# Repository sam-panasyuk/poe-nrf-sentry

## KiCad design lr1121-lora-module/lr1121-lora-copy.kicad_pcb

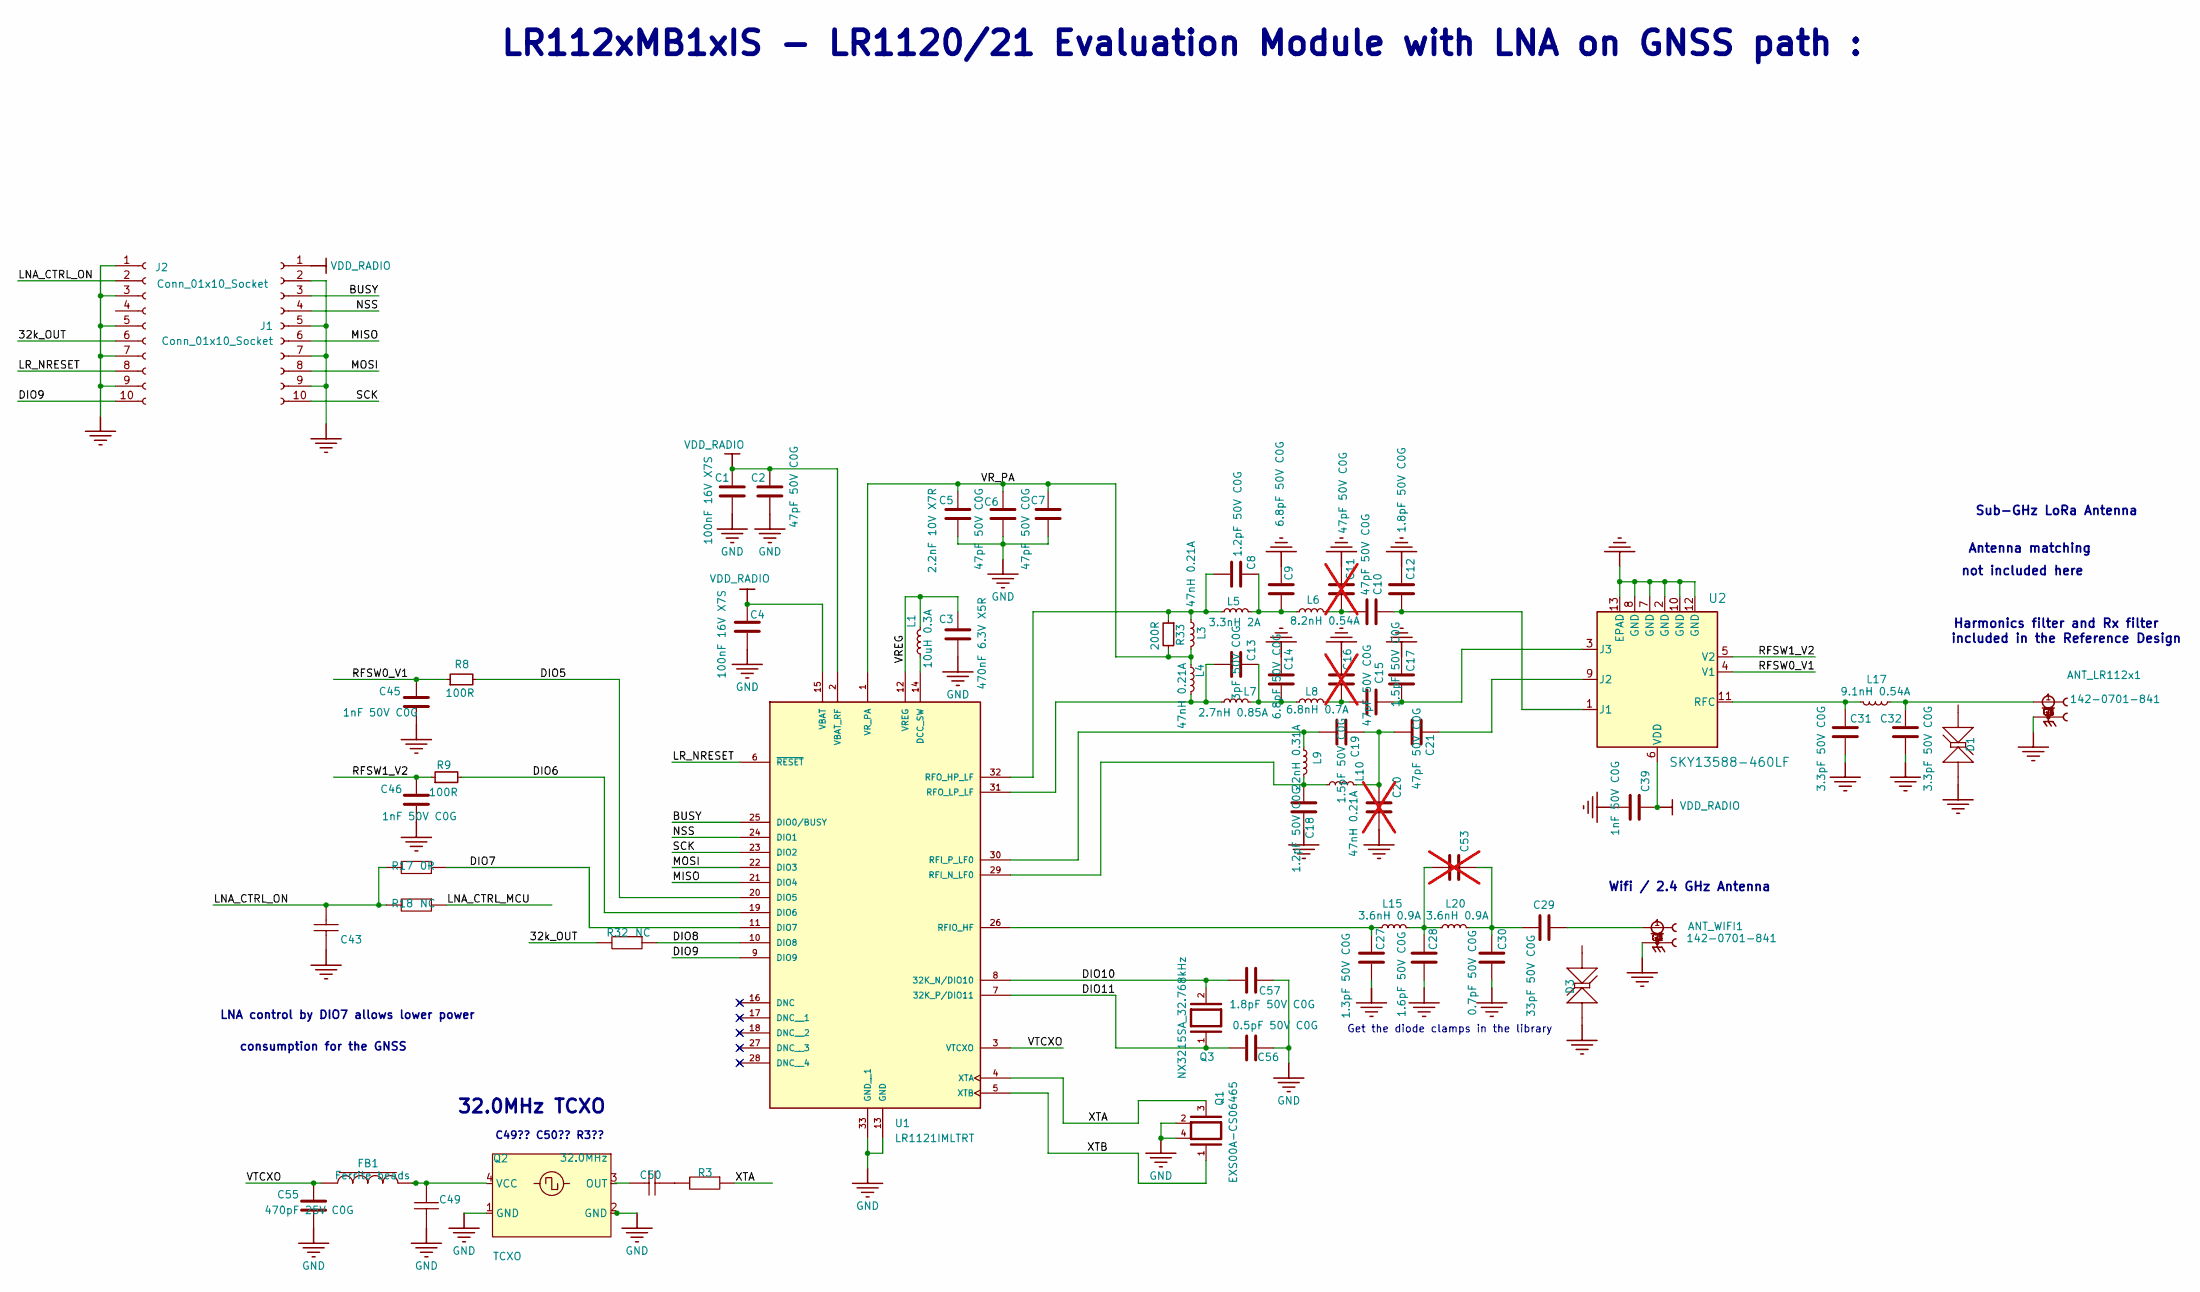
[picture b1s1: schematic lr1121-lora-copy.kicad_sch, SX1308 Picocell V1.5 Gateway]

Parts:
ANT_LR112x1: 142-0701-841; JOHNSON_142-0701-841; MPN 142-0701-841
ANT_WIFI1: 142-0701-841; JOHNSON_142-0701-841; MPN 142-0701-841
C1, C4: 100nF 16V X7S; C_0201_0603Metric; MPN GRM033C71C104ME14D; JLCPN C907967
C2, C6, C7, C10: 47pF 50V C0G; C_0201_0603Metric; MPN GRM0335C1H470GA01D; JLCPN C384994
C3: 470nF 6.3V X5R; C_0201_0603Metric; MPN GRM033R60J474KE90D; JLCPN C85926
C5: 2.2nF 10V X7R; C_0201_0603Metric; MPN GRM033R71A222KA01D; JLCPN C161479
C8, C18: 1.2pF 50V C0G; C_0402_1005Metric; MPN GRM1555C1H1R2BA01D
C9, C14: 6.8pF 50V C0G; C_0402_1005Metric; MPN GRM1555C1H6R8CA01D
C11: 47pF 50V C0G; C_0201_0603Metric; MPN GRM0335C1H470GA01D; JLCPN C384994; not fitted
C12: 1.8pF 50V C0G; C_0402_1005Metric; MPN GRM1555C1H1R8BA01D
C13: 3pF 50V C0G; C_0402_1005Metric; MPN GRM1555C1H3R0BA01J
C15, C21: 47pF 50V C0G; C_0402_1005Metric; MPN GRM1555C1H470JA01D
C16: 47pF 50V C0G; C_0402_1005Metric; MPN GRM1555C1H470JA01D; not fitted
C17, C19: 1.5pF 50V C0G; C_0402_1005Metric; MPN GRM1555C1H1R5BA01D; JLCPN C76957
C20: 1.5pF 50V C0G; C_0402_1005Metric; MPN GRM1555C1H1R5BA01D; JLCPN C76957; not fitted
C27: 1.3pF 50V C0G; C_0402_1005Metric; MPN GRM1555C1H1R3BA01D
C28: 1.6pF 50V C0G; C_0402_1005Metric; MPN GRM1555C1H1R6BA01D; JLCPN C88923
C29: 33pF 50V C0G; C_0402_1005Metric; MPN CL05C330JB5NNNC; JLCPN C70465
C30: 0.7pF 50V C0G; C_0402_1005Metric; MPN GRM1555C1HR70BA01D
C31, C32: 3.3pF 50V C0G; C_0402_1005Metric
C39, C45, C46: 1nF 50V C0G; C_0402_1005Metric; MPN C1005C0G1H102JT000F; JLCPN C343060
C43: c_201_smd
C49, C50: Cap; c_201_smd
C53: 820nF 25V X5R; C_0402_1005Metric; not fitted
C55: 470pF 25V C0G; C_0201_0603Metric; MPN GRM0335C1E471JA01D; JLCPN C161390
C56: 0.5pF 50V C0G; C_0201_0603Metric; MPN GRM0335C1HR50BA01D; JLCPN C85920
C57: 1.8pF 50V C0G; C_0201_0603Metric; MPN GRM0335C1H1R8BA01D; JLCPN C161415
D1, D3: TVS Diode; SLP0603P2X3F
FB1: Ferrite beads; Ferrite_201_smd
J1, J2: Conn_01x10_Socket; PinHeader_1x10_P2.00mm_Vertical
L1: 10uH 0.3A; L_0603_1608Metric; MPN MLZ1608N100LT000; JLCPN C194437
L3, L4, L10: 47nH 0.21A; L_0402_1005Metric; MPN LQW15AN47NJ00D; JLCPN C192855
L5: 3.3nH 2A; L_0402_1005Metric; MPN LQW15AN3N3C80D; JLCPN C237574
L6: 8.2nH 0.54A; L_0402_1005Metric; MPN LQW15AN8N2J00D; JLCPN C98066
L7: 2.7nH 0.85A; L_0402_1005Metric; MPN LQW15AN2N7C00D; JLCPN C98058
L8: 6.8nH 0.7A; L_0402_1005Metric; MPN LQW15AN6N8J00D; JLCPN C113119
L9: 22nH 0.31A; L_0402_1005Metric; MPN LQW15AN22NH00D; JLCPN C703122
L15, L20: 3.6nH 0.9A; L_0402_1005Metric; MPN LQW15AN3N6C10D; JLCPN C408158
L17: 9.1nH 0.54A; L_0402_1005Metric; MPN LQW15AN9N1J00D; JLCPN C437364
Q1: EXS00A-CS06465; Crystal_SMD_2016-4Pin_2.0x1.6mm; MPN EXS00A-CS06465; JLCPN C1986260
Q2: TCXO; TCXO 2.0x1.6mm
Q3: NX3215SA_32.768kHz; Crystal_SMD_3215-2Pin_3.2x1.5mm; MPN NX3215SA 32.768kHz; JLCPN C519280
R3, R32: Resistor; r_201_smd
R8, R9: 100R; R_0201_0603Metric; MPN RC0201FR-07100RL; JLCPN C77623
R17, R18: r_201_smd
R33: 200R; R_0201_0603Metric; MPN RC0201FR-07200RL
U1: LR1121IMLTRT; QFN-32-1EP_5x5mm_P0.5mm_EP3.7x3.7mm_ThermalVias; MPN LR1121IMLTRT; JLCPN C7498014
U2: SKY13588-460LF; QFN12_SKY; MPN SKY13588-460LF; JLCPN C2151906

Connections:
/32k_OUT: J2.6, R32.2
/BUSY: J1.3, U1.25 (DIO0/BUSY)
/DIO5: R8.2, U1.20 (DIO5)
/DIO6: R9.2, U1.19 (DIO6)
/DIO7: R17.2, U1.11 (DIO7)
/DIO8: R32.1, U1.10 (DIO8)
/DIO9: J2.10, U1.9 (DIO9)
/DIO10: C57.1, Q3.2, U1.8 (32K_N/DIO10)
/DIO11: C56.2, Q3.1, U1.7 (32K_P/DIO11)
/LNA_CTRL_MCU: R18.2
/LNA_CTRL_ON: C43.2, J2.2, R17.1, R18.1
/LR_NRESET: J2.8, U1.6 (~RESET)
/MISO: J1.6, U1.21 (DIO4)
/MOSI: J1.8, U1.22 (DIO3)
/NSS: J1.4, U1.24 (DIO1)
/RFSW0_V1: C45.2, R8.1, U2.4 (V1)
/RFSW1_V2: C46.2, R9.1, U2.5 (V2)
/SCK: J1.10, U1.23 (DIO2)
/VREG: C3.2, L1.1, U1.12 (VREG)
/VR_PA: C5.2, C6.2, C7.2, L3.2, L4.1, R33.2, U1.1 (VR_PA)
/VTCXO: C55.2, FB1.1, U1.3 (VTCXO)
/XTA: Q1.3, R3.1, U1.4 (XTA)
/XTB: Q1.1, U1.5 (XTB)
GND: ANT_LR112x1.G1, ANT_LR112x1.G2, ANT_LR112x1.G3, ANT_LR112x1.G4, ANT_WIFI1.G1, ANT_WIFI1.G2, ANT_WIFI1.G3, ANT_WIFI1.G4, C1.1, C2.1, C3.1, C4.1, C5.1, C6.1, C7.1, C9.2, C11.2, C12.2, C14.2, C16.2, C17.2, C18.1, C20.1, C27.1, C28.1, C30.1, C31.2, C32.2, C39.1, C43.1, C45.1, C46.1, C49.1, C55.1, C56.1, C57.2, D1.1 (A_1), D3.1 (A_1), J1.2, J1.5, J1.7, J1.9, J2.1, J2.3, J2.5, J2.7, J2.9, Q1.2, Q1.4, Q2.1 (GND), Q2.2 (GND), U1.13 (GND), U1.33 (GND__1), U2.2 (GND), U2.7 (GND), U2.8 (GND), U2.10 (GND), U2.12 (GND), U2.13 (EPAD)
unnamed: ANT_LR112x1.1, C32.1, L17.2
unnamed: ANT_WIFI1.1, C29.2
unnamed: C8.2, C9.1, L5.2, L6.1
unnamed: C10.1, C11.1, L6.2
unnamed: C13.2, C14.1, L7.2, L8.1
unnamed: C15.1, C16.1, L8.2
unnamed: C19.2, C20.2, C21.2, L10.2
unnamed: C28.2, C53.1, L15.2, L20.1
unnamed: C29.1, C30.2, C53.2, L20.2
unnamed: C49.2, FB1.2
unnamed: C50.2 (2_2), R3.2
unnamed: L1.2, U1.14 (DCC_SW)
unnamed: C27.2, L15.1, U1.26 (RFIO_HF)
unnamed: C18.2, L9.2, L10.1, U1.29 (RFI_N_LF0)
unnamed: C19.1, L9.1, U1.30 (RFI_P_LF0)
unnamed: C8.1, L3.1, L5.1, R33.1, U1.32 (RFO_HP_LF)
unnamed: C13.1, L4.2, L7.1, U1.31 (RFO_LP_LF)
unnamed: C10.2, C12.1, U2.1 (J1)
unnamed: C21.1, U2.9 (J2)
unnamed: C15.2, C17.1, U2.3 (J3)
unnamed: C31.1, L17.1, U2.11 (RFC)
VDD_RADIO: C1.2, C2.2, C4.2, C39.2, J1.1, U1.2 (VBAT_RF), U1.15 (VBAT), U2.6 (VDD)

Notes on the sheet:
consumption for the GNSS
32.0MHz TCXO
Get the diode clamps in the library
Antenna matching
Sub-GHz LoRa Antenna
Harmonics filter and Rx filter
included in the Reference Design
LR112xMB1xIS - LR1120/21 Evaluation Module with LNA on GNSS path :
C49?? C50?? R3??
LNA control by DIO7 allows lower power
not included here
Wifi / 2.4 GHz Antenna

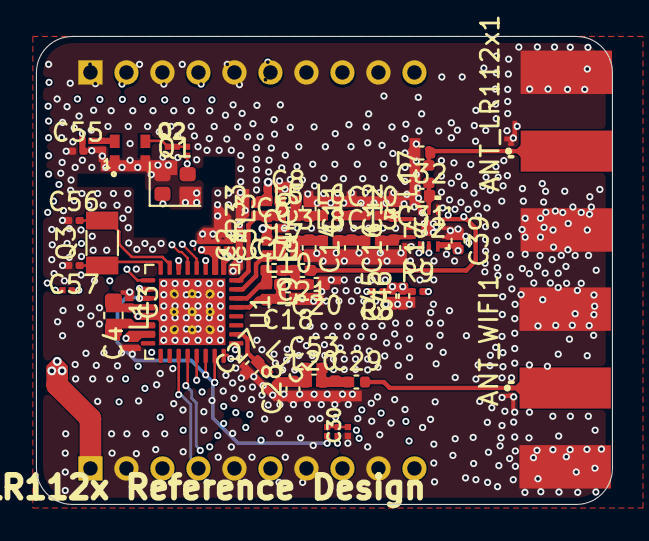
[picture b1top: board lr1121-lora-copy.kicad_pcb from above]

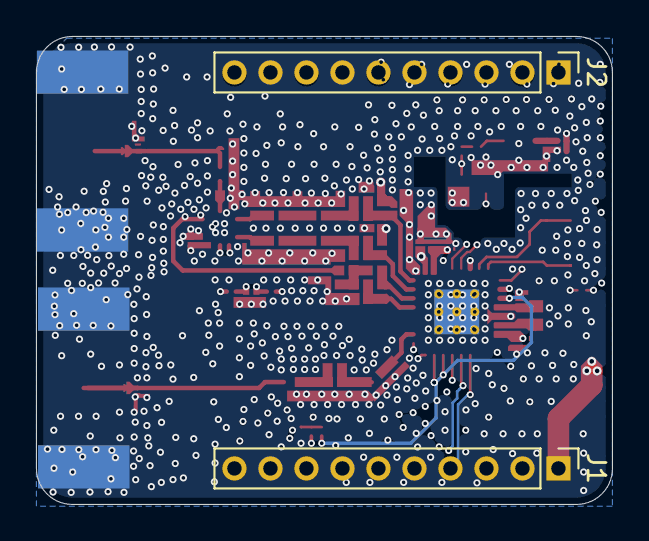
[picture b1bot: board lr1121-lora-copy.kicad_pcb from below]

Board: 4 copper layers, 32.0 x 26.0 mm, 68 parts (2 on the bottom side), 45 nets.

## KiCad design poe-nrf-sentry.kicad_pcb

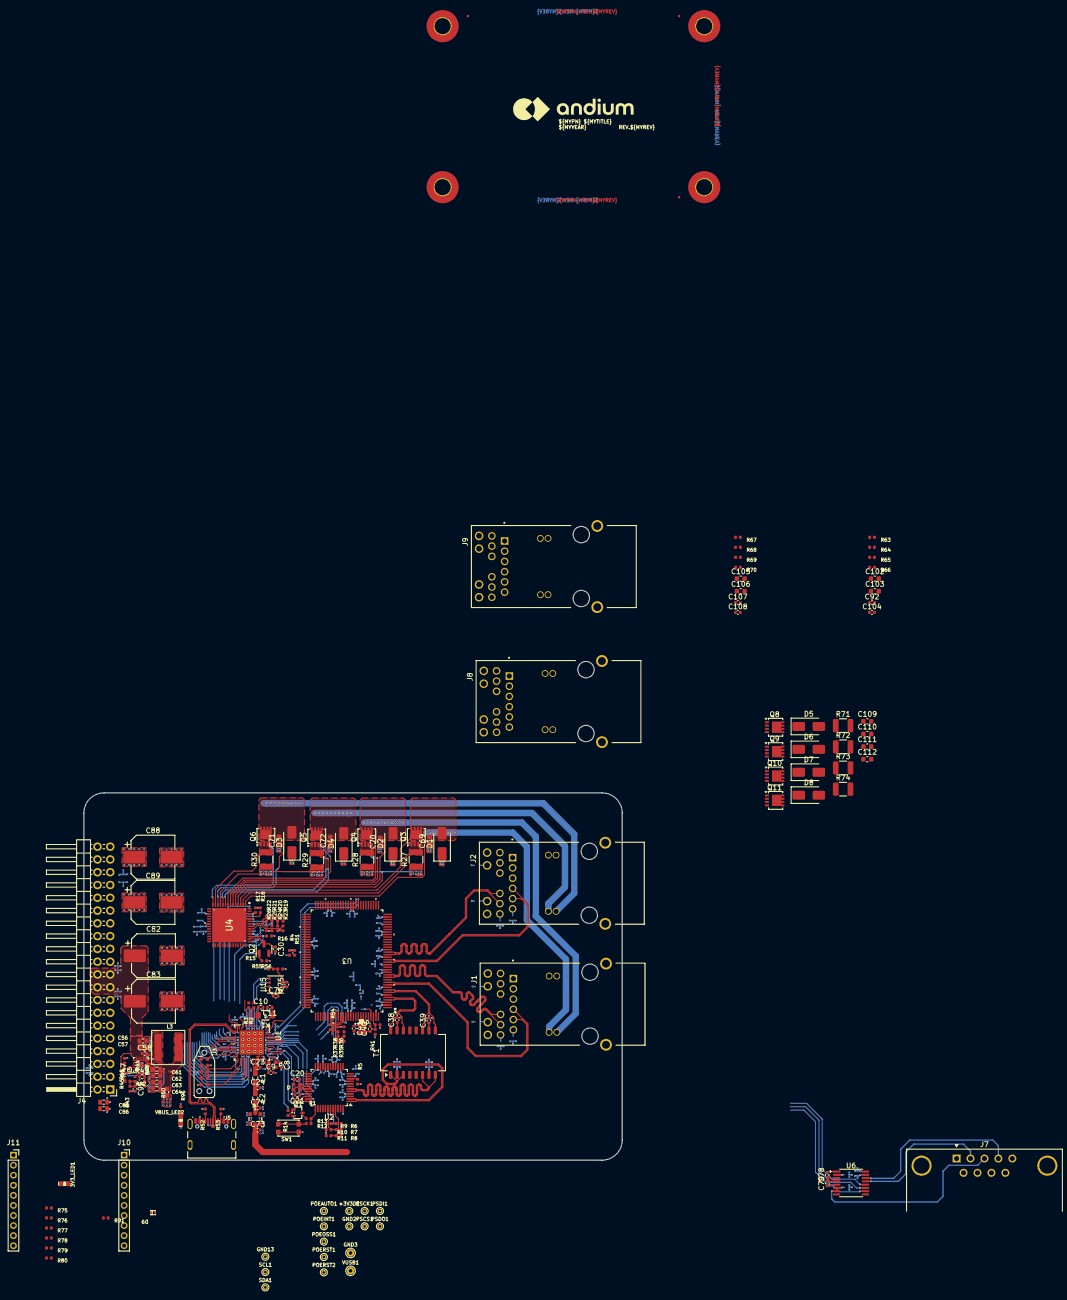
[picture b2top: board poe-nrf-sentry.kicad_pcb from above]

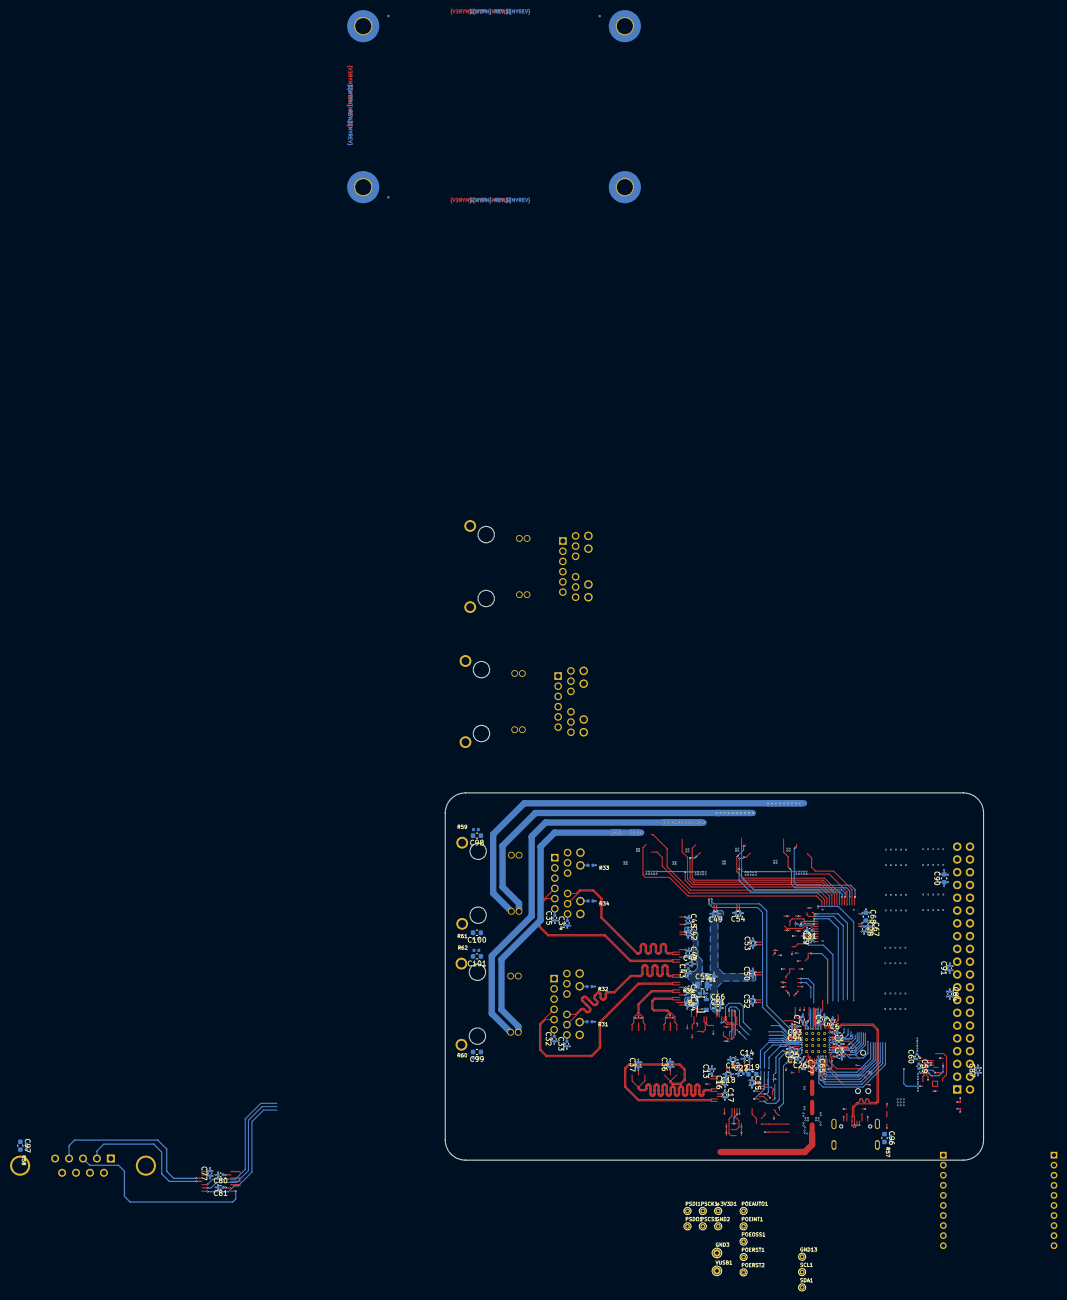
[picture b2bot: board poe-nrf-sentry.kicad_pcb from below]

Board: 6 copper layers, 107.0 x 73.0 mm, 270 parts (79 on the bottom side), 177 nets.

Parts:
3V3_LED1: LTST-C190GKT; LED_0603_1608Metric_G
+3V3D1: TestPoint_1mm_0.5mm_TH; TestPoint_THTPad_D1.0mm_Drill0.5mm
C1, C2, C3, C7, C25, C27, C28, C29, C30, C31, C32, C33, C34, C35, C36, C37, C38, C39, C58, C60, C75, C76, C77, C78, C79, C80, C81, C84, C87, C91, C92, C95, C104, C107, C108: 100nF 50V X7R; C_0402_1005Metric
C4, C5, C6, C22: 4.7uF 16V X5R; C_0402_1005Metric
C8, C9, C10, C11: 12pF 50V C0G; C_0402_1005Metric
C12, C13, C14, C15, C16, C17, C18, C42, C43, C44, C45, C46, C47, C48, C49, C50, C51, C52, C53, C54, C59, C93, C94: 1uF 25V X5R; C_0402_1005Metric
C19: 10nF 50V C0G; C_0603_1608Metric
C20, C21: 18pF 50V C0G; C_0402_1005Metric
C23: 1pF 50V C0G; C_0402_1005Metric
C24, C73, C74: 1.2pF 50V C0G; C_0402_1005Metric
C26: 100pF 50V C0G; C_0402_1005Metric
C40, C41: 15pF 50V C0G; C_0402_1005Metric
C55: 47uF 10V X5R; C_0805_2012Metric
C56, C57, C61, C62, C63, C64, C85, C86: 22uF 16V X5R; C_0603_1608Metric
C65: 820pF 50V C0G; C_0402_1005Metric
C66, C67: 10uF 10V X5R; C_0402_1005Metric
C68, C69, C70, C71, C72, C90, C96, C97, C98, C99, C100, C101, C102, C103, C105, C106, C109, C110, C111, C112: 100nF 100V X7R; C_0603_1608Metric
C82, C83: 220uF 35V; CP_Elec_8x10.5
C88, C89: 22uF 100V; CP_Elec_8x10.5
D1, D2, D3, D4, D5, D6, D7, D8: TVS 93.6V 4.3A; D_SMA
D9: ESD9X5.0ST5G; SOD-923
FB1: 600R 1A; FB_0603_1608Metric
FID1, FID2, FID3, FID4, FID5, FID6: FID_0.5MM_1MM_MASK; Fiducial_0.5mm_Mask1mm
GND2, GND13: TestPoint_1mm_0.5mm_TH; TestPoint_THTPad_D1.0mm_Drill0.5mm
GND3: TestPoint_1.5mm_0.7mm_TH; TestPoint_THTPad_D1.5mm_Drill0.7mm
H1, H2, H3, H4: MTG_PAD_3.2MM; MountingHole_3.2mm_M3_Pad_TopBottom
J1, J2, J8, J9: RJ45; BEL_0826-1X1T-GH-F
J3: TAG-CONN; Tag-Connect_TC2050-IDC-NL_2x5_P1.27mm
J4: Conn_02x20_Odd_Even; PinHeader_2x20_P2.54mm_Horizontal
J5: USB-C; USB-C_Receptacle_GCT_USB4105-GF-A
J6: MM8130-2600RA2; MURATA_MM8130-2600RA2
J7: DSUB DB9 MALE; DSUB-9_Pins_Horizontal_P2.77x2.84mm_EdgePinOffset7.70mm_Hou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
J10, J11: Conn_01x10_Socket; PinSocket_1x10_P2.00mm_Vertical
L1: 4.7nH 1.5A; L_0603_1608Metric
L2: 2.2nH 3.2A; L_0603_1608Metric
L3: 1.8uH 14A; L_Coilcraft-XAL6030
POEAUTO1: TP 1mm; TestPoint_THTPad_D1.0mm_Drill0.5mm
POEINT1: TP 1mm; TestPoint_THTPad_D1.0mm_Drill0.5mm
POEOSS1: TP 1mm; TestPoint_THTPad_D1.0mm_Drill0.5mm
POERST1, POERST2: TP 1mm; TestPoint_THTPad_D1.0mm_Drill0.5mm
PSCK1: TP 1mm; TestPoint_THTPad_D1.0mm_Drill0.5mm
PSCS1: TP 1mm; TestPoint_THTPad_D1.0mm_Drill0.5mm
PSDI1: TP 1mm; TestPoint_THTPad_D1.0mm_Drill0.5mm
PSDO1: TP 1mm; TestPoint_THTPad_D1.0mm_Drill0.5mm
Q1: NPN 40V 0.2A; SOT-323_SC-70
Q2: N-CH 25V 0.22A; FDV301N
Q3, Q4, Q5, Q6, Q8, Q9, Q10, Q11: N-CH 100V 30A; LFPAK33
Q7: P-CH 30V 6A; SOT-23-3
R1, R2, R3, R54: 22R1; R_0402_1005Metric
R4, R51: 4k75; R_0402_1005Metric
R5: 12k4; R_0402_1005Metric
R6, R7, R8, R9, R10, R11, R15, R16, R17, R18, R46: 10k; R_0402_1005Metric
R12, R13: 3k32; R_0402_1005Metric
R14: 2k21; R_0402_1005Metric
R19, R20, R21, R22, R23, R24, R25, R26, R35, R36, R37, R38, R56, R91: 1k02; R_0402_1005Metric
R27, R28, R29, R30, R71, R72, R73, R74: 0R2; R_1210_3225Metric
R31, R32, R33, R34, R65, R66, R69, R70: 6k19; R_0402_1005Metric
R39: 100R; R_0402_1005Metric
R40: 2k05; R_0402_1005Metric
R41: 4k02; R_0402_1005Metric
R42: 182k; R_0402_1005Metric
R43: 51k1; R_0402_1005Metric
R44, R75, R76, R77, R78, R79, R80: 0R; R_0402_1005Metric
R45: R_220k_0402; R_0402_1005Metric
R47: 100k; R_0402_1005Metric
R48: 90k9; R_0402_1005Metric
R49: 20k5; R_0402_1005Metric
R50: R_0R_22.4A_0603; R_0603_1608Metric
R52, R53: 5k6; R_0402_1005Metric
R55: 1k; R_0402_1005Metric
R57, R58, R59, R60, R61, R62, R63, R64, R67, R68: 976k; R_0402_1005Metric
R96: 1k62; R_0402_1005Metric
SCL1: TestPoint_1mm_0.5mm_TH; TestPoint_THTPad_D1.0mm_Drill0.5mm
SDA1: TestPoint_1mm_0.5mm_TH; TestPoint_THTPad_D1.0mm_Drill0.5mm
SW1: SW_KMR211NGLFS_SMD
T1: S558-5999-U7-F; Transformer_Ethernet_CNDtek_H1102N
U1: NRF52840-QIAA-R; XCVR_NRF52840-QIAA-R
U2: W5500; LQFP-48_7x7mm_P0.5mm
U3: KSZ8895RQXI-TR; PQFP-128_MQL_MCH
U4: Si3474B-A01-IMR; QFN50P800X800X90-57N
U5: 12A; QFN-20-1EP_3x3mm_P0.45mm_TPS56xxxx
U6: RS232_16-TSSOP_MAX3232IPWR; TSSOP-16_4.4x5mm_P0.65mm
U15: BME688; Bosch_LGA-8_3x3mm_P0.8mm_ClockwisePinNumbering
VBUS_LED2: LTST-C190GKT; LED_0603_1608Metric_G
VUSB1: TestPoint_1.5mm_0.7mm_TH; TestPoint_THTPad_D1.5mm_Drill0.7mm
X1: MU00525-32.768K; XTAL_MU00525_NDK
Y1: XRCGB32M000F2P01R0; XRCGB25M000FAM10R0
Y2, Y3: XRCGB25M000FAM10R0

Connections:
1V2: C42.1, C43.1, C44.1, C55.1, FB1.1, Q7.3 (D), R39.2, U3.3 (VDDAR), U3.15 (VDDAR), U3.31 (VDDAR)
1V2F: C49.1, C50.1, C51.1, C66.1, FB1.2, U3.50 (VDDC), U3.89 (VDDC), U3.117 (VDDC)
1V2_W5500: C19.1, U2.22 (1V20)
+3V3D: +3V3D1.1 (1_1), C1.1, C2.1, C3.1, C4.1, C12.1, C13.1, C14.1, C15.1, C16.1, C17.1, C18.1, C28.1, C29.1, C36.1, C37.1, C45.1, C46.1, C47.1, C48.1, C52.1, C53.1, C54.1, C67.1, C75.2, C76.2, C77.2, C85.1, C86.1, C87.1, C93.1, D9.1 (C), J4.2, J4.4, Q7.2 (S), R4.2, R6.2, R7.2, R8.2, R16.2, R17.2, R18.2, R19.2, R20.2, R21.2, R22.2, R31.2, R32.2, R33.2, R34.2, R35.2, R37.2, R39.1, R41.2, R50.2, R51.2, R55.2, R65.2, R66.2, R69.2, R70.2, R91.2, T1.2, T1.7, U1.A22 (VDD), U1.AD14 (VDD__1), U1.AD23 (VDD__2), U1.B1 (VDD__3), U1.W1 (VDD__4), U1.Y2 (VDDH), U2.4 (AVDD), U2.8 (AVDD), U2.11 (AVDD), U2.15 (AVDD), U2.17 (AVDD), U2.21 (AVDD), U2.28 (VDD), U3.9 (VDDAT), U3.18 (VDDAT), U3.24 (VDDAT), U3.37 (VDDAT), U3.59 (VDDIO), U3.77 (VDDIO), U3.100 (VDDIO), U4.22 (VDDA), U4.43 (VDD), U6.16 (VCC), U15.2 (CSB), U15.6 (VDDIO), U15.8 (VDD)
+12VD: C56.2, C57.2, C58.1, C82.1, C83.1, C84.1, C91.1, J4.17, J4.18, J4.19, J4.20, R42.1, U5.2 (V_{IN}), U5.3 (V_{IN}), U5.4 (V_{IN}), U5.5 (V_{IN})
+VPOE: C68.1, C69.1, C70.1, C71.1, C72.1, C88.1, C89.1, C90.1, C109.1, C110.1, C111.1, C112.1, D1.1 (C), D2.1 (C), D3.1 (C), D4.1 (C), D5.1 (C), D6.1 (C), D7.1 (C), D8.1 (C), J1.13 (V1), J1.15 (V3), J2.13 (V1), J2.15 (V3), J4.33, J4.35, J4.37, J8.13 (V1), J8.15 (V3), J9.13 (V1), J9.15 (V3), U4.17 (VPWR)
/eth-port1/LEDG: J1.20, U3.101 (LED2-2)
/eth-port1/LEDY: J1.17, U3.103 (LED2-0)
/eth-port1/POE_AM: C69.2, D1.2 (A), J1.14 (V2), Q3.5 (D), U4.3 (DRAIN1)
/eth-port1/POE_BM: C70.2, D2.2 (A), J1.16 (V4), Q4.5 (D), U4.5 (DRAIN2)
/eth-port1/RX_N: J1.5 (D2-), U3.11 (RXM2)
/eth-port1/RX_P: J1.4 (D2+), U3.10 (RXP2)
/eth-port1/TX_N: J1.10 (D1-), U3.14 (TXM2)
/eth-port1/TX_P: J1.11 (D1+), U3.13 (TXP2)
/eth-port2/LEDG: J2.20, U3.96 (LED3-2)
/eth-port2/LEDY: J2.17, U3.98 (LED3-0)
/eth-port2/POE_AM: C72.2, D4.2 (A), J2.14 (V2), Q5.5 (D), U4.10 (DRAIN3)
/eth-port2/POE_BM: C71.2, D3.2 (A), J2.16 (V4), Q6.5 (D), U4.12 (DRAIN4)
/eth-port2/RX_N: J2.5 (D2-), U3.20 (RXM3)
/eth-port2/RX_P: J2.4 (D2+), U3.19 (RXP3)
/eth-port2/TX_N: J2.10 (D1-), U3.23 (TXM3)
/eth-port2/TX_P: J2.11 (D1+), U3.22 (TXP3)
/eth-port3/LEDG: J8.20, U3.93 (LED4-2)
/eth-port3/LEDY: J8.17, U3.95 (LED4-0)
/eth-port3/POE_AM: C109.2, D5.2 (A), J8.14 (V2), Q8.5 (D), U4.31 (DRAIN5)
/eth-port3/POE_BM: C110.2, D6.2 (A), J8.16 (V4), Q9.5 (D), U4.33 (DRAIN6)
/eth-port3/RX_N: J8.5 (D2-), U3.26 (RXM4)
/eth-port3/RX_P: J8.4 (D2+), U3.25 (RXP4)
/eth-port3/TX_N: J8.10 (D1-), U3.29 (TXM4)
/eth-port3/TX_P: J8.11 (D1+), U3.28 (TXP4)
/eth-port4/LEDG: J9.20, U3.90 (LED5-2)
/eth-port4/LEDY: J9.17, U3.92 (LED5-0)
/eth-port4/POE_AM: C112.2, D8.2 (A), J9.14 (V2), Q10.5 (D), U4.38 (DRAIN7)
/eth-port4/POE_BM: C111.2, D7.2 (A), J9.16 (V4), Q11.5 (D), U4.40 (DRAIN8)
/eth-port4/RX_N: J9.5 (D2-), U3.33 (RXM5)
/eth-port4/RX_P: J9.4 (D2+), U3.32 (RXP5)
/eth-port4/TX_N: J9.10 (D1-), U3.36 (TXM5)
/eth-port4/TX_P: J9.11 (D1+), U3.35 (TXP5)
/eth-sw/MISO: J4.7, PSDO1.1 (1_1), R1.1, R54.1, U1.L1 (P0.06)
/eth-sw/MOSI: J4.5, PSDI1.1 (1_1), R2.1, U2.35 (MOSI), U3.111 (SPID/SDA)
/eth-sw/PS0: R37.1, R38.2, U3.114 (PS0)
/eth-sw/PS1: R35.1, R36.2, U3.113 (PS1)
/eth-sw/PWRSEL: R40.2, R41.1, U3.126 (IN_PWR_SEL)
/eth-sw/SCK: J4.3, PSCK1.1 (1_1), R3.1, U2.33 (SCLK), U3.110 (SPIC/SCL)
/eth-sw/W5500.RX_N: T1.14, U3.5 (RXM1)
/eth-sw/W5500.RX_P: T1.16, U3.4 (RXP1)
/eth-sw/W5500.TX_N: T1.9, U3.8 (TXM1)
/eth-sw/W5500.TX_P: T1.11, U3.7 (TXP1)
/eth-sw/~CS: U1.A16 (P1.13), U3.112 (SPIS_N)
/eth-sw/~INT: U1.P23 (P1.07), U3.48 (INTR_N)
/eth-sw/~PWRD: U1.A14 (P1.15), U3.47 (PWRDN_N)
/eth-sw/~RST: U1.B15 (P1.14), U3.115 (RST_N)
/nrf52840/DEC1: C7.1, U1.C1 (DEC1)
/nrf52840/DEC2: C25.1, U1.A18 (DEC2)
/nrf52840/DEC3: C26.1, U1.D23 (DEC3)
/nrf52840/DEC5: C65.1, U1.N24 (DEC5)
/nrf52840/DEC46: C27.1, C94.1, U1.B5 (DEC4), U1.E24 (DEC6)
/nrf52840/NRESET: J3.10, U1.AC13 (P0.18/NRESET)
/nrf52840/PMODE0: R8.1, R11.2, U2.45 (PMODE0)
/nrf52840/PMODE1: R7.1, R10.2, U2.44 (PMODE1)
/nrf52840/PMODE2: R6.1, R9.2, U2.43 (PMODE2)
/nrf52840/POE.AUTO: POEAUTO1.1 (1_1), U1.V23 (P1.03), U4.52 (AUTO)
/nrf52840/POE.OSS: POEOSS1.1 (1_1), U1.W24 (P1.02), U4.56 (OSS)
/nrf52840/POE.RST: POERST1.1 (1_1), Q2.1 (G), R15.2, U1.T23 (P1.05)
/nrf52840/POE.SCL: R18.1, SCL1.1 (1_1), U1.K2 (P0.05/AIN3), U4.53 (SCL), U15.4 (SCK)
/nrf52840/POE.SDA: R17.1, SDA1.1 (1_1), U1.J1 (P0.04/AIN2), U4.54 (SDA), U15.3 (SDI)
/nrf52840/POE.~INT: POEINT1.1 (1_1), R16.1, U1.U24 (P1.04), U4.45 (INTB)
/nrf52840/PSU.RS232_DTR: J4.13, R75.2
/nrf52840/PSU.RS232_RX: J4.12, R77.2
/nrf52840/PSU.RS232_TX: J4.14, R76.2
/nrf52840/PSU.~CS: J4.1, PSCS1.1 (1_1), U1.R24 (P1.06)
/nrf52840/RF1: C23.1, L1.1, U1.H23 (ANT)
/nrf52840/RF2: C24.1, L1.2, L2.1
/nrf52840/RF3: C74.1, J6.1 (IN), L2.2
/nrf52840/RF4: C73.1, J6.2 (OUT)
/nrf52840/RS232_DTR: R75.1, R78.1, U6.14 (T1OUT)
/nrf52840/RS232_RX: R77.1, R80.1, U6.13 (R1IN)
/nrf52840/RS232_TX: R76.1, R79.1, U6.7 (T2OUT)
/nrf52840/RX_N: T1.8, U2.5 (RXN)
/nrf52840/RX_P: T1.6, U2.6 (RXP)
/nrf52840/SWDCLK: J3.4, U1.AA24 (SWDCLK)
/nrf52840/SWDIO: J3.2, U1.AC24 (SWDIO)
/nrf52840/SWO: J3.6, U1.AD22 (P1.00/TRACEDATA0)
/nrf52840/TX_N: T1.3, U2.1 (TXN)
/nrf52840/TX_P: T1.1, U2.2 (TXP)
/nrf52840/USB2.0_N: J5.A7 (D_{A}-), J5.B7 (D_{B}-), U1.AD4 (D-)
/nrf52840/USB2.0_P: J5.A6 (D_{A}+), J5.B6 (D_{B}+), U1.AD6 (D+)
/nrf52840/W5500_RST_MCU: R14.1, U1.B19 (P1.11)
/nrf52840/XC1: C9.1, U1.B24 (XC1), Y1.3
/nrf52840/XC2: C8.1, U1.A23 (XC2), Y1.1
/nrf52840/XI: C20.2, U2.30 (XI/CLKIN), Y2.3
/nrf52840/XL1: C11.1, U1.D2 (P0.00/XL1), X1.1
/nrf52840/XL2: C10.1, U1.F2 (P0.01/XL2), X1.2
/nrf52840/XO: C21.2, U2.31 (XO), Y2.1
/nrf52840/~W5500_CS: U1.A20 (P1.10), U2.32 (SCSN)
/nrf52840/~W5500_INTN: U1.B17 (P1.12), U2.36 (INTN)
/nrf52840/~W5500_RST: R12.2, R13.2, U2.37 (RSTN)
/poe-controller/A1: R19.1, R23.2, U4.48 (A1)
/poe-controller/A2: R20.1, R24.2, U4.49 (A2)
/poe-controller/A3: R21.1, R25.2, U4.50 (A3)
/poe-controller/A4: R22.1, R26.2, U4.51 (A4)
/poe-controller/CAP_POE: C31.1, U4.47 (DECPL)
/poe-controller/G1: Q3.4 (G), U4.1 (GATE1)
/poe-controller/G2: Q4.4 (G), U4.7 (GATE2)
/poe-controller/G3: Q5.4 (G), U4.8 (GATE3)
/poe-controller/G4: Q6.4 (G), U4.14 (GATE4)
/poe-controller/G5: Q8.4 (G), U4.29 (GATE5)
/poe-controller/G6: Q9.4 (G), U4.35 (GATE6)
/poe-controller/G7: Q10.4 (G), U4.36 (GATE7)
/poe-controller/G8: Q11.4 (G), U4.42 (GATE8)
/poe-controller/S1: Q3.1 (S), Q3.2 (S), Q3.3 (S), R27.2, U4.2 (SOURCE1)
/poe-controller/S2: Q4.1 (S), Q4.2 (S), Q4.3 (S), R28.2, U4.6 (SOURCE2)
/poe-controller/S3: Q5.1 (S), Q5.2 (S), Q5.3 (S), R29.2, U4.9 (SOURCE3)
/poe-controller/S4: Q6.1 (S), Q6.2 (S), Q6.3 (S), R30.2, U4.13 (SOURCE4)
/poe-controller/S5: Q8.1 (S), Q8.2 (S), Q8.3 (S), R71.2, U4.30 (SOURCE5)
/poe-controller/S6: Q9.1 (S), Q9.2 (S), Q9.3 (S), R72.2, U4.34 (SOURCE6)
/poe-controller/S7: Q10.1 (S), Q10.2 (S), Q10.3 (S), R73.2, U4.37 (SOURCE7)
/poe-controller/S8: Q11.1 (S), Q11.2 (S), Q11.3 (S), R74.2, U4.41 (SOURCE8)
/poe-controller/~RSTB_POE: C30.1, POERST2.1 (1_1), Q2.3 (D), U4.44 (RESETB)
/psu-ctrl/3V3_EN: R44.2, U5.12 (EN)
/psu-ctrl/3V3_FB: R48.2, R49.2, U5.14 (FB)
/psu-ctrl/3V3_OUT: C61.2, C62.2, C63.2, C64.2, L3.2, R48.1, R50.1
/psu-ctrl/3V3_SW: C60.1, L3.1, U5.6 (SW), U5.19 (SW), U5.20 (SW)
CHGND: C96.2, C97.2, C98.2, C99.2, C100.2, C101.2, C102.2, C103.2, C105.2, C106.2, J1.S1 (SHIELD1), J1.S2 (SHIELD2), J2.S1 (SHIELD1), J2.S2 (SHIELD2), J5.SH, J7.SH (PAD), J8.S1 (SHIELD1), J8.S2 (SHIELD2), J9.S1 (SHIELD1), J9.S2 (SHIELD2), R57.2, R58.2, R59.2, R60.2, R61.2, R62.2, R63.2, R64.2, R67.2, R68.2
GND: 3V3_LED1.1 (C), C1.2, C2.2, C3.2, C4.2, C5.2, C6.2, C7.2, C8.2, C9.2, C10.2, C11.2, C12.2, C13.2, C14.2, C15.2, C16.2, C17.2, C18.2, C19.2, C20.1, C21.1, C22.1, C23.2, C24.2, C25.2, C26.2, C27.2, C28.2, C29.2, C30.2, C31.2, C32.1, C33.1, C34.1, C35.1, C36.2, C37.2, C38.2, C39.2, C40.2, C41.2, C42.2, C43.2, C44.2, C45.2, C46.2, C47.2, C48.2, C49.2, C50.2, C51.2, C52.2, C53.2, C54.2, C55.2, C56.1, C57.1, C58.2, C59.1, C61.1, C62.1, C63.1, C64.1, C65.2, C66.2, C67.2, C73.2, C74.2, C75.1, C76.1, C77.1, C80.2, C81.2, C82.2, C83.2, C84.2, C85.2, C86.2, C87.2, C91.2, C92.1, C93.2, C94.2, C95.2, C96.1, C97.1, C98.1, C99.1, C100.1, C101.1, C102.1, C103.1, C104.1, C105.1, C106.1, C107.1, C108.1, D9.2 (A), GND2.1 (1_1), GND3.1 (1_1), GND13.1 (1_1), H1.1 (1_1), H2.1 (1_1), H3.1 (1_1), H4.1 (1_1), J3.3, J3.5, J3.9, J4.6, J4.8, J4.15, J4.16, J4.21, J4.22, J5.A1 (GND), J5.A12 (GND), J5.B1 (GND), J5.B12 (GND), J6.G1 (GND), J6.G2 (GND__1), J6.G3 (GND__2), J6.G4 (GND__3), J7.5, J10.1, J10.3, J10.5, J10.7, J10.9, J11.2, J11.5, J11.7, J11.9, Q1.2 (E), Q2.2 (S), R5.1, R9.1, R10.1, R11.1, R15.1, R23.1, R24.1, R25.1, R26.1, R36.1, R38.1, R40.1, R43.2, R46.1, R49.1, R52.1, R53.1, R56.1, R57.1, R58.1, R59.1, R60.1, R61.1, R62.1, R63.1, R64.1, R67.1, R68.1, SW1.1, SW1.2, U1.74 (VSS), U1.B7 (VSS__1), U1.F23 (VSS_PA), U2.3 (AGND), U2.9 (AGND), U2.14 (AGND), U2.16 (AGND), U2.19 (AGND), U2.23 (RSVD(GND)), U2.29 (DGND), U2.42 (RSVD), U2.48 (AGND), U3.2 (GNDA), U3.6 (GNDA), U3.12 (GNDA), U3.16 (GNDA), U3.21 (GNDA), U3.27 (GNDA), U3.30 (GNDA), U3.34 (GNDA), U3.49 (GNDD), U3.58 (GNDD), U3.76 (GNDD), U3.88 (GNDD), U3.99 (GNDD), U3.116 (GNDD), U3.127 (GNDA), U4.46 (DGND), U4.57 (EP), U5.7 (PGND), U5.8 (PGND), U5.13 (AGND), U5.18 (PGND), U5.21 (PGND), U6.15 (GND), U15.1 (GND), U15.7 (GND), VBUS_LED2.1 (C)
unnamed: 3V3_LED1.2 (A), R91.1
unnamed: C38.1, T1.15
unnamed: C39.1, T1.10
unnamed: C95.1, R42.2, R43.1, R44.1
unnamed: C33.2, J1.12 (CD1)
unnamed: C32.2, J1.6 (CD2)
unnamed: J1.18, R32.1
unnamed: J1.19, R31.1
unnamed: C34.2, J2.12 (CD1)
unnamed: C35.2, J2.6 (CD2)
unnamed: J2.18, R33.1
unnamed: J2.19, R34.1
unnamed: J5.A5 (CC_{1}), R52.2
unnamed: J5.B5 (CC_{2}), R53.2
unnamed: J7.2, R80.2
unnamed: J7.3, R79.2
unnamed: J7.4, R78.2
unnamed: C92.2, J8.12 (CD1)
unnamed: C104.2, J8.6 (CD2)
unnamed: J8.18, R65.1
unnamed: J8.19, R66.1
unnamed: C107.2, J9.12 (CD1)
unnamed: C108.2, J9.6 (CD2)
unnamed: J9.18, R69.1
unnamed: J9.19, R70.1
unnamed: Q1.1 (B), R14.2
unnamed: Q1.3 (C), R13.1
unnamed: Q7.1 (G), U3.125 (LDO_O)
unnamed: R12.1, SW1.3, SW1.4
unnamed: C6.1, U1.AC5 (DECUSB)
unnamed: R2.2, U1.M2 (P0.07/TRACECLK)
unnamed: R3.2, U1.N1 (P0.08)
unnamed: R5.2, U2.10 (EXRES1)
unnamed: R1.2, U2.34 (MISO)
unnamed: C22.2, U2.20 (TOCAP)
unnamed: R54.2, U3.109 (SPIQ)
unnamed: C41.1, U3.121 (X1), Y3.1
unnamed: C40.1, U3.122 (X2), Y3.3
unnamed: C60.2, U5.1 (BST)
unnamed: R45.1, R46.2, U5.15 (MODE)
unnamed: R47.2, U5.9 (PG)
unnamed: C59.2, R45.2, R47.1, U5.17 (V_{CC})
unnamed: C78.2, U6.1 (C1+)
unnamed: C78.1, U6.3 (C1-)
unnamed: C79.2, U6.4 (C2+)
unnamed: C79.1, U6.5 (C2-)
unnamed: C80.1, U6.2 (VS+)
unnamed: C81.1, U6.6 (VS-)
unnamed: R55.1, R56.2, U15.5 (SDO)
unnamed: R96.1, VBUS_LED2.2 (A)
PGND: C68.2, C88.2, C89.2, C90.2, J4.34, J4.36, J4.38, R27.1, R28.1, R29.1, R30.1, R71.1, R72.1, R73.1, R74.1, U4.4 (KSENSA), U4.11 (KSENSB), U4.21 (AGND), U4.32 (KSENSC), U4.39 (KSENSD)
VBUS: C5.1, J5.A4 (VBUS), J5.A9 (VBUS), J5.B4 (VBUS), J5.B9 (VBUS), R96.2, U1.AD2 (VBUS), VUSB1.1 (1_1)

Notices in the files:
parts and their libraries:
License: Apache-2.0
